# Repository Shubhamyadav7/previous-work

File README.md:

# previous-work
PDB stands for power distribution board made for our robot for robocon
"robocoon" is our main control board which controls rhino motors LSA's solenoid valves etc
"h bridge" is a dual h bridge which can control 2 DC motors independently in any desired direction

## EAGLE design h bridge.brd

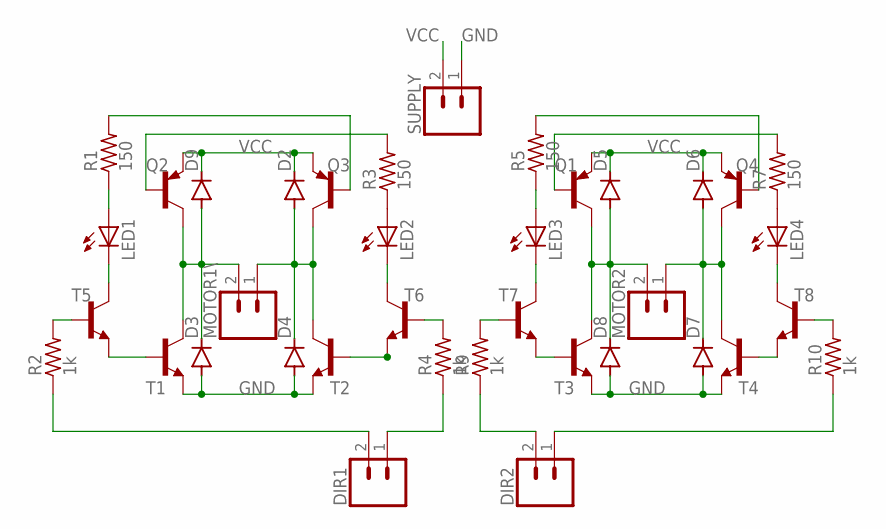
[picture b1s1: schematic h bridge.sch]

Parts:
D2, D3, D4, D5, D6, D7, D8, D9: DIODE-D-2.5; D-2.5
DIR1, DIR2: CONN_02; 1X02
LED1, LED2, LED3, LED4: LED3MM
MOTOR1\, MOTOR2: CONN_02; 1X02
Q1, Q2, Q3, Q4: 2N2907; TO92-EBC-OVAL
R1, R3, R5, R7: 150; 0204/7
R2, R4, R9, R10: 1k; 0204/7
SUPPLY: CONN_02; 1X02
T1, T2, T3, T4, T5, T6, T7, T8: 2N2222; TO92-EBC-OVAL

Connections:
GND: D3.A, D4.A, D7.A, D8.A, SUPPLY.1, T1.E, T2.E, T3.E, T4.E
unnamed: T3.B, T7.E
unnamed: Q3.B, R1.2
unnamed: Q1.B, R7.2
unnamed: LED2.A, R3.1
unnamed: Q2.B, R3.2
unnamed: Q4.B, R5.2
unnamed: LED4.A, R7.1
unnamed: T2.B, T6.E
unnamed: LED1.A, R1.1
unnamed: LED1.K (C), T5.C
unnamed: R2.2, T5.B
unnamed: T4.B, T8.E
unnamed: R4.2, T6.B
unnamed: R9.2, T7.B
unnamed: R10.2, T8.B
unnamed: DIR1.2, R2.1
unnamed: D3.C, D9.A, MOTOR1\.2, Q2.C, T1.C
unnamed: D2.A, D4.C, MOTOR1\.1, Q3.C, T2.C
unnamed: D5.A, D8.C, MOTOR2.2, Q1.C, T3.C
unnamed: D6.A, D7.C, MOTOR2.1, Q4.C, T4.C
unnamed: DIR1.1, R4.1
unnamed: DIR2.2, R9.1
unnamed: DIR2.1, R10.1
unnamed: LED2.K (C), T6.C
unnamed: LED3.K (C), T7.C
unnamed: LED3.A, R5.1
unnamed: LED4.K (C), T8.C
unnamed: T1.B, T5.E
VCC: D2.C, D5.C, D6.C, D9.C, Q1.E, Q2.E, Q3.E, Q4.E, SUPPLY.2

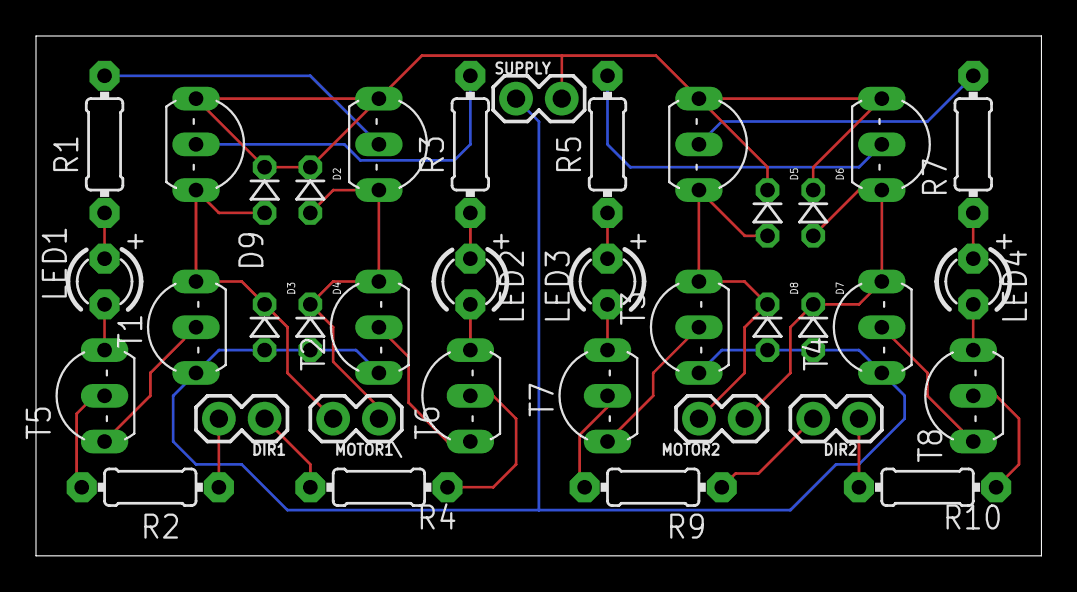
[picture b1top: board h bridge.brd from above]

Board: 2 copper layers, 55.9 x 28.9 mm, 37 parts (0 on the bottom side), 30 nets.

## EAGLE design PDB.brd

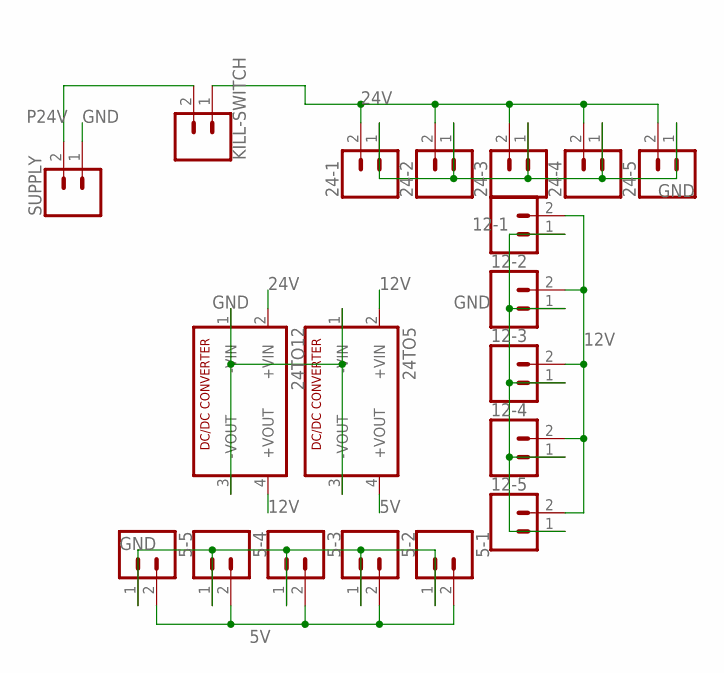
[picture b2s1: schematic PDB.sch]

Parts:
5-1, 5-2, 5-3, 5-4, 5-5, 12-1, 12-2, 12-3, 12-4, 12-5, 24-1, 24-2, 24-3, 24-4, 24-5: CONN_02; 1X02
24TO5, 24TO12: NME
KILL-SWITCH: CONN_02; 1X02
SUPPLY: CONN_02; 1X02

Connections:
5V: 5-1.2, 5-2.2, 5-3.2, 5-4.2, 5-5.2, 24TO5.4 (+VOUT)
12V: 12-1.2, 12-2.2, 12-3.2, 12-4.2, 12-5.2, 24TO5.2 (+VIN), 24TO12.4 (+VOUT)
24V: 24-1.2, 24-2.2, 24-3.2, 24-4.2, 24-5.2, 24TO12.2 (+VIN), KILL-SWITCH.1
GND: 5-1.1, 5-2.1, 5-3.1, 5-4.1, 5-5.1, 12-1.1, 12-2.1, 12-3.1, 12-4.1, 12-5.1, 24-1.1, 24-2.1, 24-3.1, 24-4.1, 24-5.1, 24TO5.1 (-VIN), 24TO5.3 (-VOUT), 24TO12.1 (-VIN), 24TO12.3 (-VOUT), SUPPLY.1
P24V: KILL-SWITCH.2, SUPPLY.2

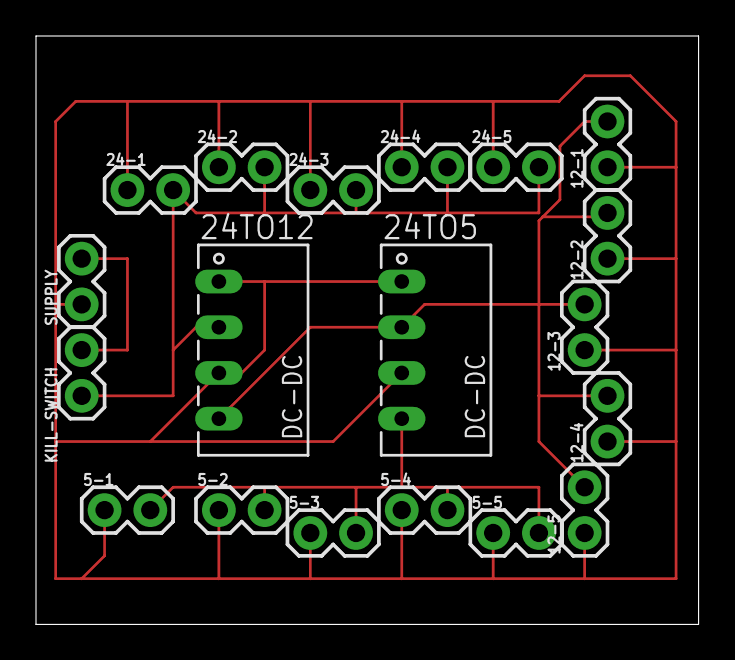
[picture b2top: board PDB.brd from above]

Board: 2 copper layers, 36.8 x 32.7 mm, 19 parts (0 on the bottom side), 5 nets.

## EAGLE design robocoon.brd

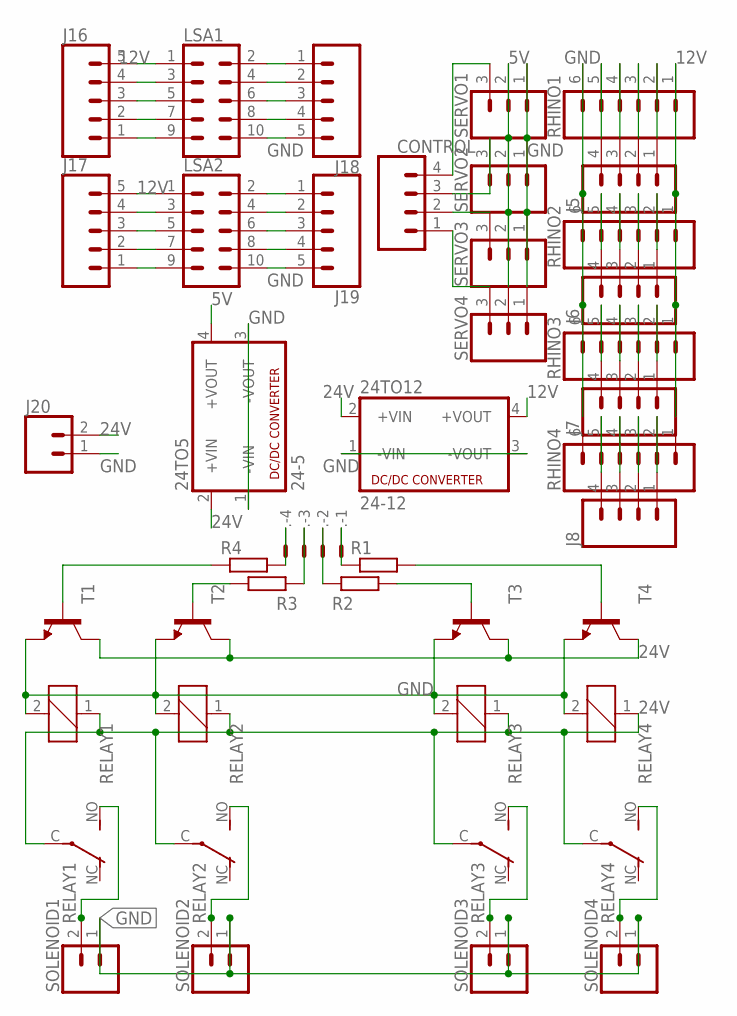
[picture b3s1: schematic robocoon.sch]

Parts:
24TO5: 24-5; NME
24TO12: 24-12; NME
.: 22-23-2041
CONTROL: CONN_04; 1X04
J5, J6, J7, J8: CONN_04; 1X04
J16, J17, J18, J19: CONN_05SCREW; SCREWTERMINAL-3.5MM-5
J20: CONN_023.5MM; SCREWTERMINAL-3.5MM-2
LSA1, LSA2: CONN_05X2PTH; 2X5
R1, R2, R3, R4: R-EU_0204/2V; 0204V
RELAY1, RELAY2, RELAY3, RELAY4: CQ1-12V; CQ1
RHINO1, RHINO2, RHINO3, RHINO4: CONN_06NO_SILK_FEMALE_PTH; 1X06_NO_SILK
SERVO1, SERVO2, SERVO3, SERVO4: CONN_03SCREW; SCREWTERMINAL-3.5MM-3
SOLENOID1, SOLENOID2, SOLENOID3, SOLENOID4: CONN_023.5MM; SCREWTERMINAL-3.5MM-2
T1, T2, T3, T4: -NPN-TO92; TO92

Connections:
5V: 24TO5.4 (+VOUT), SERVO1.2, SERVO2.2, SERVO3.2, SERVO4.2
12V: 24TO12.4 (+VOUT), J16.5, J17.5, LSA1.1, LSA2.1, RHINO1.1, RHINO2.1, RHINO3.1, RHINO4.1
24V: 24TO5.2 (+VIN), 24TO12.2 (+VIN), J20.2, RELAY1.1, RELAY1.C, RELAY2.1, RELAY2.C, RELAY3.1, RELAY3.C, RELAY4.1, RELAY4.C, T1.3 (C), T2.3 (C), T3.3 (C), T4.3 (C)
GND: 24TO5.1 (-VIN), 24TO5.3 (-VOUT), 24TO12.1 (-VIN), 24TO12.3 (-VOUT), J18.5, J19.5, J20.1, LSA1.10, LSA2.10, RELAY1.2, RELAY2.2, RELAY3.2, RELAY4.2, RHINO1.6, RHINO2.6, RHINO3.6, RHINO4.6, SERVO1.1, SERVO2.1, SERVO3.1, SERVO4.1, SOLENOID1.1, SOLENOID2.1, SOLENOID3.1, SOLENOID4.1, T1.1 (E), T2.1 (E), T3.1 (E), T4.1 (E)
unnamed: J5.4, RHINO1.5
unnamed: J5.3, RHINO1.4
unnamed: J5.2, RHINO1.3
unnamed: J5.1, RHINO1.2
unnamed: J6.4, RHINO2.5
unnamed: J6.3, RHINO2.4
unnamed: J6.2, RHINO2.3
unnamed: J6.1, RHINO2.2
unnamed: J7.1, RHINO3.2
unnamed: J7.2, RHINO3.3
unnamed: J7.3, RHINO3.4
unnamed: J7.4, RHINO3.5
unnamed: J8.1, RHINO4.2
unnamed: J8.2, RHINO4.3
unnamed: J8.3, RHINO4.4
unnamed: J8.4, RHINO4.5
unnamed: CONTROL.4, SERVO1.3
unnamed: CONTROL.1, SERVO4.3
unnamed: CONTROL.2, SERVO3.3
unnamed: CONTROL.3, SERVO2.3
unnamed: ..4, R4.2
unnamed: ..3, R3.2
unnamed: ..2, R2.1
unnamed: ..1, R1.1
unnamed: J16.1, LSA1.9
unnamed: R4.1, T1.2 (B)
unnamed: R3.1, T2.2 (B)
unnamed: J16.2, LSA1.7
unnamed: R2.2, T3.2 (B)
unnamed: R1.2, T4.2 (B)
unnamed: J16.3, LSA1.5
unnamed: J16.4, LSA1.3
unnamed: J18.1, LSA1.2
unnamed: J18.2, LSA1.4
unnamed: J18.3, LSA1.6
unnamed: J18.4, LSA1.8
unnamed: RELAY1.NO (S), SOLENOID1.2
unnamed: RELAY2.NO (S), SOLENOID2.2
unnamed: RELAY3.NO (S), SOLENOID3.2
unnamed: RELAY4.NO (S), SOLENOID4.2
unnamed: J17.4, LSA2.3
unnamed: J17.3, LSA2.5
unnamed: J17.2, LSA2.7
unnamed: J17.1, LSA2.9
unnamed: J19.1, LSA2.2
unnamed: J19.2, LSA2.4
unnamed: J19.3, LSA2.6
unnamed: J19.4, LSA2.8

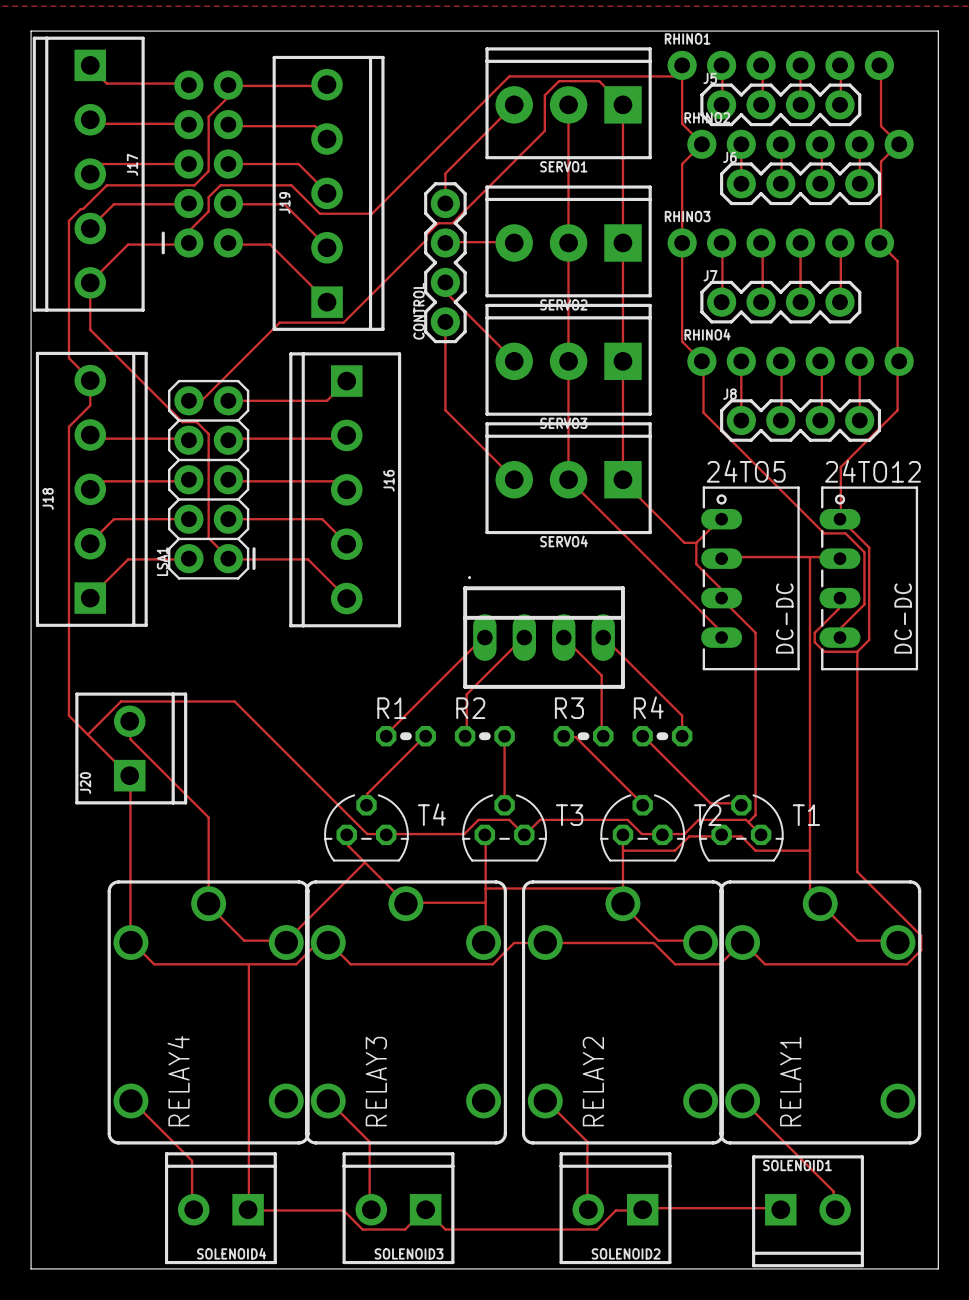
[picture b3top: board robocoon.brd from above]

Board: 2 copper layers, 58.4 x 79.7 mm, 39 parts (1 on the bottom side), 52 nets.

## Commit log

2020-06-20 Create eagle boards
2020-06-20 Add files via upload
    PDB stands for power distribution board which was made for our robot for robocon
    "robocoon" is the main circuit board for controlling motors LSA's solenoid valves etc
    "h bridge" is the design for a dual h bridge for controlling 2 motors in any desired direction

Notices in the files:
parts and their libraries:
SparkFun-Connectors: Licensing: Creative Commons ShareAlike 4.0 International - https://creativecommons.org/licenses/by-sa/4.0
